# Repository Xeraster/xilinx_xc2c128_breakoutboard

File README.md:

a standalone breakout board for Xilinx xc2c128-7tqg144i cplds

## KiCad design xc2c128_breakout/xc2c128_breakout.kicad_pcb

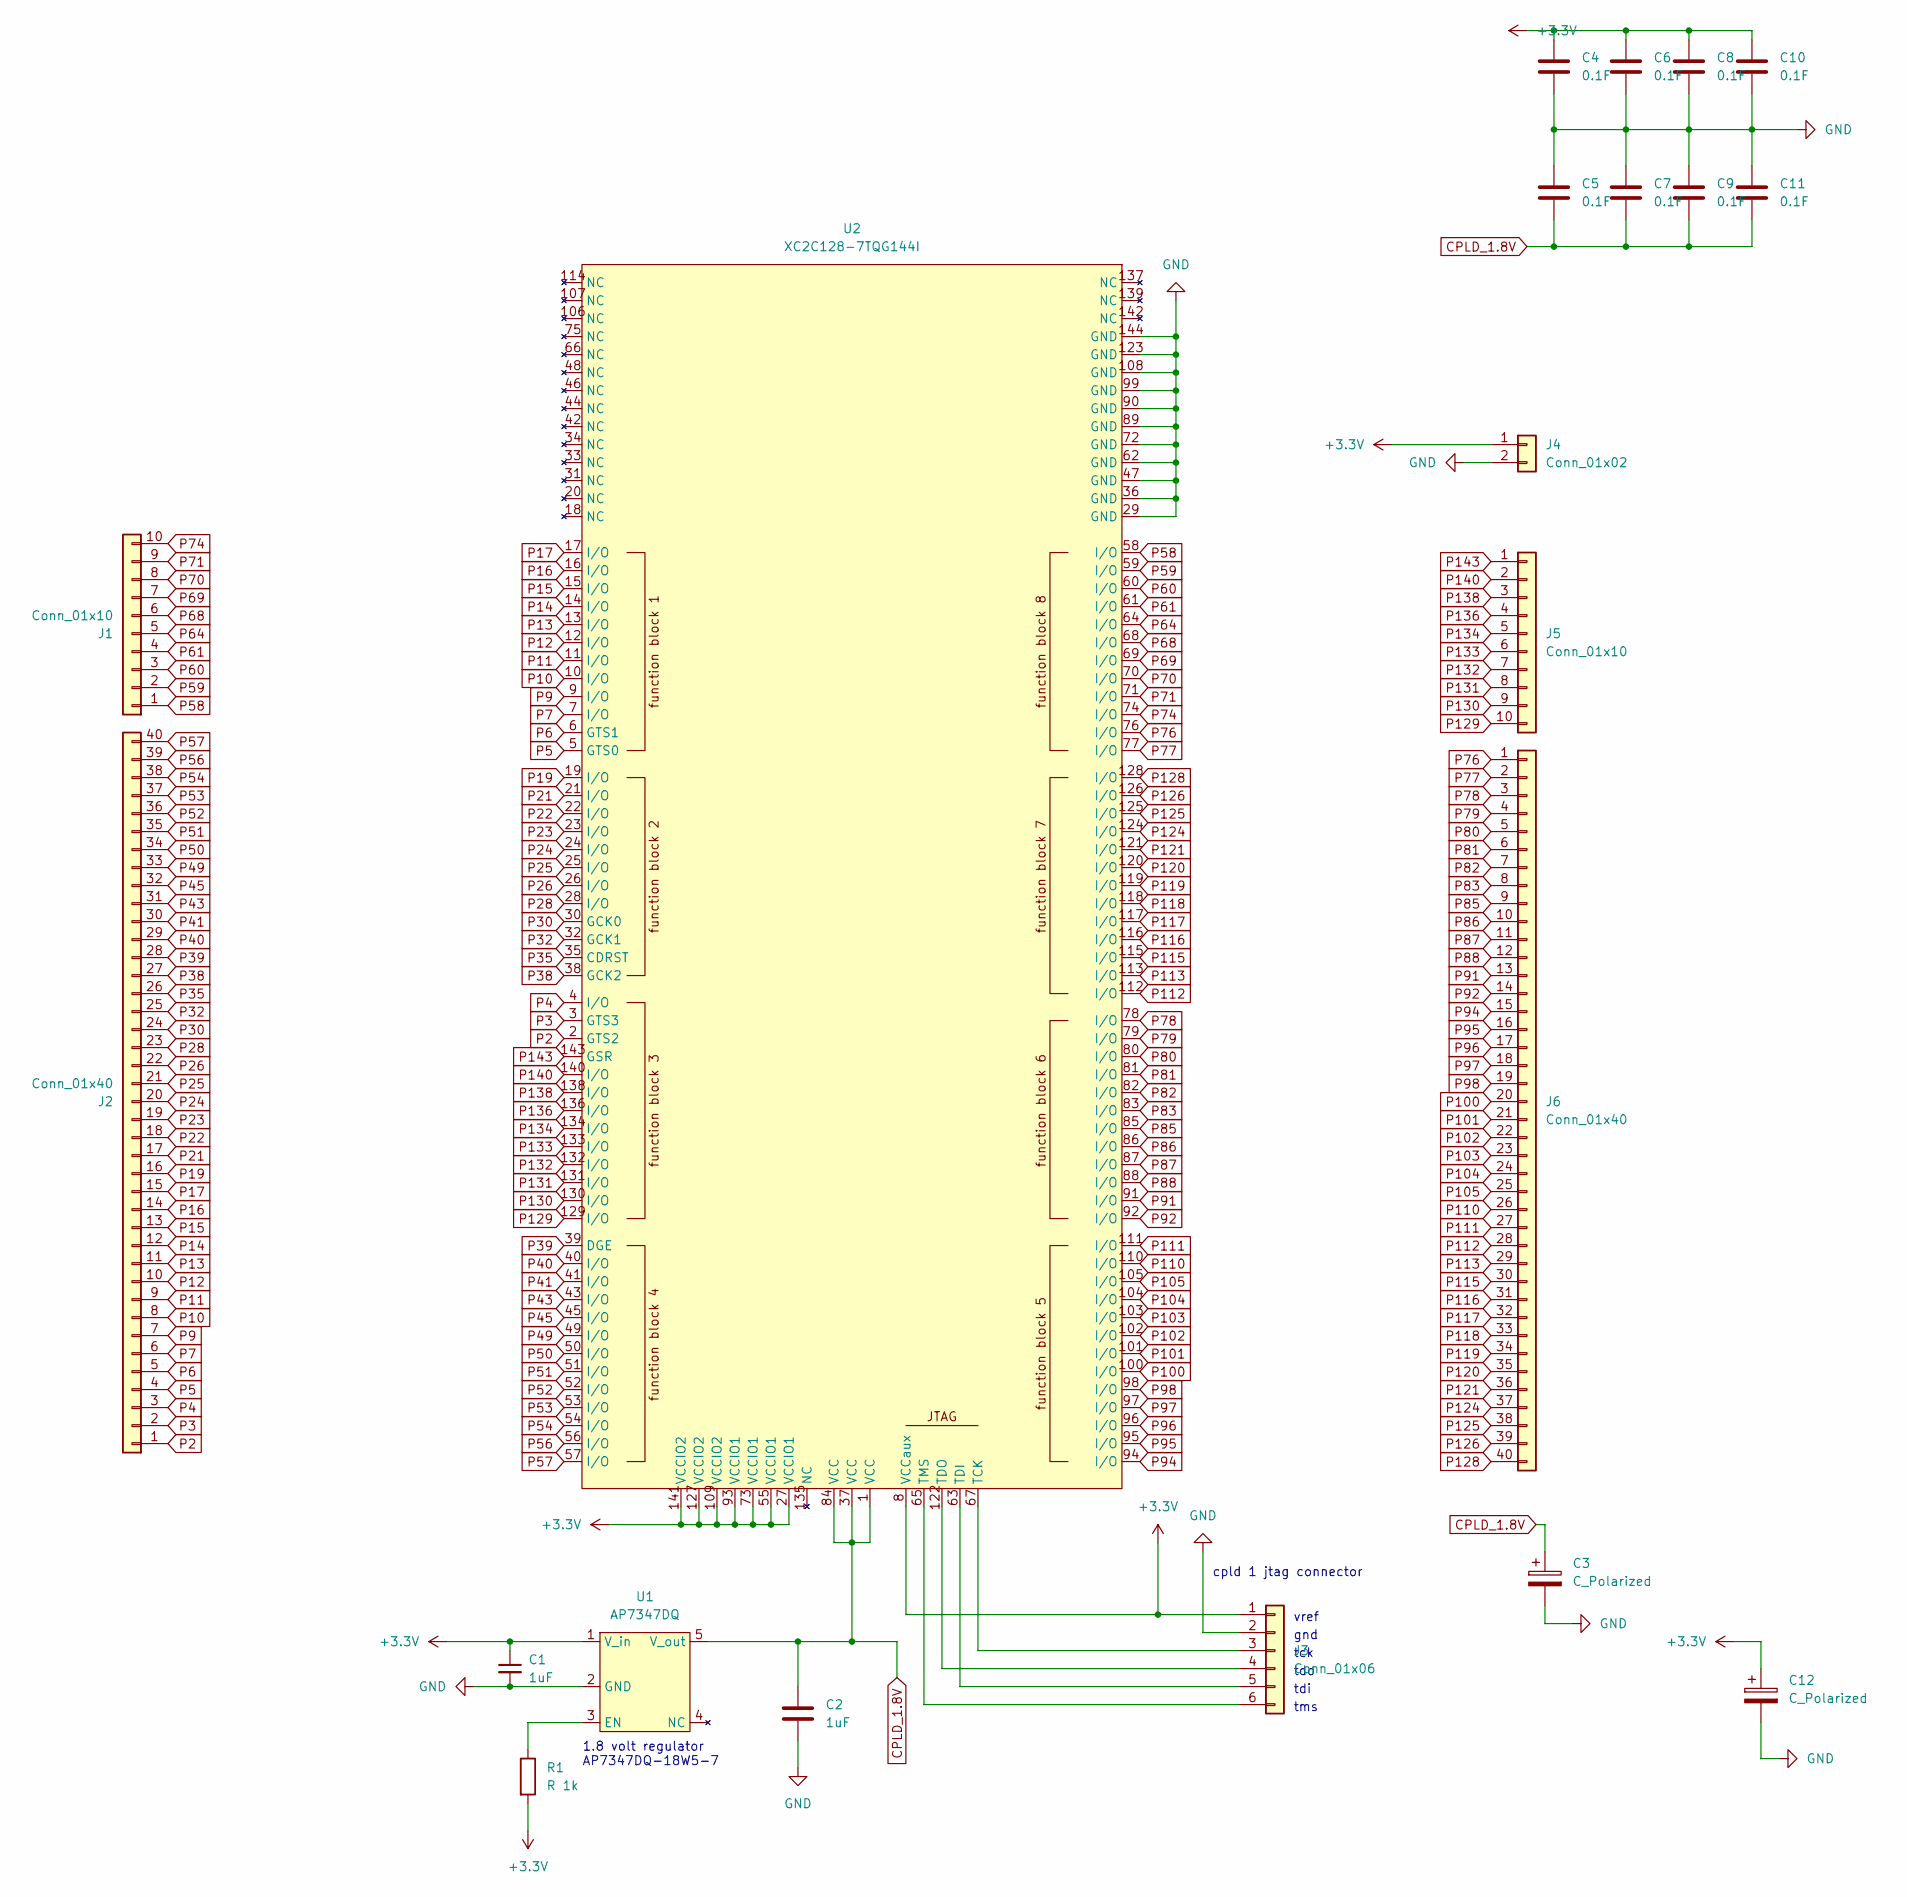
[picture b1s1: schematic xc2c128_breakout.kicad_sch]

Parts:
C1, C2: 1uF; C_Disc_D5.0mm_W2.5mm_P5.00mm
C3, C12: C_Polarized; CP_Radial_D5.0mm_P2.50mm
C4, C5, C6, C7, C8, C9, C10, C11: 0.1F; C_Disc_D5.0mm_W2.5mm_P5.00mm
J1, J5: Conn_01x10; PinHeader_1x10_P2.54mm_Vertical
J2, J6: Conn_01x40; PinHeader_1x40_P2.54mm_Vertical
J3: Conn_01x06; PinHeader_1x06_P2.54mm_Vertical
J4: Conn_01x02; PinHeader_1x02_P2.54mm_Vertical
R1: R 1k; R_Axial_DIN0207_L6.3mm_D2.5mm_P10.16mm_Horizontal
U1: AP7347DQ; SOT25
U2: XC2C128-7TQG144I; TQFP-144_20x20mm_P0.5mm

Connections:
+3.3V: C1.1, C4.1, C6.1, C8.1, C10.1, C12.1, J3.1, J4.1, R1.2, U1.1 (V_in), U2.8 (VCCaux), U2.27 (VCCIO1), U2.55 (VCCIO1), U2.73 (VCCIO1), U2.93 (VCCIO1), U2.109 (VCCIO2), U2.127 (VCCIO2), U2.141 (VCCIO2)
CPLD_1.8V: C2.1, C3.1, C5.2, C7.2, C9.2, C11.2, U1.5 (V_out), U2.1 (VCC), U2.37 (VCC), U2.84 (VCC)
GND: C1.2, C2.2, C3.2, C4.2, C5.1, C6.2, C7.1, C8.2, C9.1, C10.2, C11.1, C12.2, J3.2, J4.2, U1.2 (GND), U2.29 (GND), U2.36 (GND), U2.47 (GND), U2.62 (GND), U2.72 (GND), U2.89 (GND), U2.90 (GND), U2.99 (GND), U2.108 (GND), U2.123 (GND), U2.144 (GND)
unnamed: J3.3, U2.67 (TCK)
unnamed: J3.4, U2.122 (TDO)
unnamed: J3.5, U2.63 (TDI)
unnamed: J3.6, U2.65 (TMS)
unnamed: R1.1, U1.3 (EN)
P2: J2.1, U2.2 (GTS2)
P3: J2.2, U2.3 (GTS3)
P4: J2.3, U2.4 (I/O)
P5: J2.4, U2.5 (GTS0)
P6: J2.5, U2.6 (GTS1)
P7: J2.6, U2.7 (I/O)
P9: J2.7, U2.9 (I/O)
P10: J2.8, U2.10 (I/O)
P11: J2.9, U2.11 (I/O)
P12: J2.10, U2.12 (I/O)
P13: J2.11, U2.13 (I/O)
P14: J2.12, U2.14 (I/O)
P15: J2.13, U2.15 (I/O)
P16: J2.14, U2.16 (I/O)
P17: J2.15, U2.17 (I/O)
P19: J2.16, U2.19 (I/O)
P21: J2.17, U2.21 (I/O)
P22: J2.18, U2.22 (I/O)
P23: J2.19, U2.23 (I/O)
P24: J2.20, U2.24 (I/O)
P25: J2.21, U2.25 (I/O)
P26: J2.22, U2.26 (I/O)
P28: J2.23, U2.28 (I/O)
P30: J2.24, U2.30 (GCK0)
P32: J2.25, U2.32 (GCK1)
P35: J2.26, U2.35 (CDRST)
P38: J2.27, U2.38 (GCK2)
P39: J2.28, U2.39 (DGE)
P40: J2.29, U2.40 (I/O)
P41: J2.30, U2.41 (I/O)
P43: J2.31, U2.43 (I/O)
P45: J2.32, U2.45 (I/O)
P49: J2.33, U2.49 (I/O)
P50: J2.34, U2.50 (I/O)
P51: J2.35, U2.51 (I/O)
P52: J2.36, U2.52 (I/O)
P53: J2.37, U2.53 (I/O)
P54: J2.38, U2.54 (I/O)
P56: J2.39, U2.56 (I/O)
P57: J2.40, U2.57 (I/O)
P58: J1.1, U2.58 (I/O)
P59: J1.2, U2.59 (I/O)
P60: J1.3, U2.60 (I/O)
P61: J1.4, U2.61 (I/O)
P64: J1.5, U2.64 (I/O)
P68: J1.6, U2.68 (I/O)
P69: J1.7, U2.69 (I/O)
P70: J1.8, U2.70 (I/O)
P71: J1.9, U2.71 (I/O)
P74: J1.10, U2.74 (I/O)
P76: J6.1, U2.76 (I/O)
P77: J6.2, U2.77 (I/O)
P78: J6.3, U2.78 (I/O)
P79: J6.4, U2.79 (I/O)
P80: J6.5, U2.80 (I/O)
P81: J6.6, U2.81 (I/O)
P82: J6.7, U2.82 (I/O)
P83: J6.8, U2.83 (I/O)
P85: J6.9, U2.85 (I/O)
P86: J6.10, U2.86 (I/O)
P87: J6.11, U2.87 (I/O)
P88: J6.12, U2.88 (I/O)
P91: J6.13, U2.91 (I/O)
P92: J6.14, U2.92 (I/O)
P94: J6.15, U2.94 (I/O)
P95: J6.16, U2.95 (I/O)
P96: J6.17, U2.96 (I/O)
P97: J6.18, U2.97 (I/O)
P98: J6.19, U2.98 (I/O)
P100: J6.20, U2.100 (I/O)
P101: J6.21, U2.101 (I/O)
P102: J6.22, U2.102 (I/O)
P103: J6.23, U2.103 (I/O)
P104: J6.24, U2.104 (I/O)
P105: J6.25, U2.105 (I/O)
P110: J6.26, U2.110 (I/O)
P111: J6.27, U2.111 (I/O)
P112: J6.28, U2.112 (I/O)
P113: J6.29, U2.113 (I/O)
P115: J6.30, U2.115 (I/O)
P116: J6.31, U2.116 (I/O)
P117: J6.32, U2.117 (I/O)
P118: J6.33, U2.118 (I/O)
P119: J6.34, U2.119 (I/O)
P120: J6.35, U2.120 (I/O)
P121: J6.36, U2.121 (I/O)
P124: J6.37, U2.124 (I/O)
P125: J6.38, U2.125 (I/O)
P126: J6.39, U2.126 (I/O)
P128: J6.40, U2.128 (I/O)
P129: J5.10, U2.129 (I/O)
P130: J5.9, U2.130 (I/O)
P131: J5.8, U2.131 (I/O)
P132: J5.7, U2.132 (I/O)
P133: J5.6, U2.133 (I/O)
P134: J5.5, U2.134 (I/O)
P136: J5.4, U2.136 (I/O)
P138: J5.3, U2.138 (I/O)
P140: J5.2, U2.140 (I/O)
P143: J5.1, U2.143 (GSR)

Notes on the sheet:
tdo
vref
1.8 volt regulator AP7347DQ-18W5-7
tdi
tms
tck
cpld 1 jtag connector
gnd

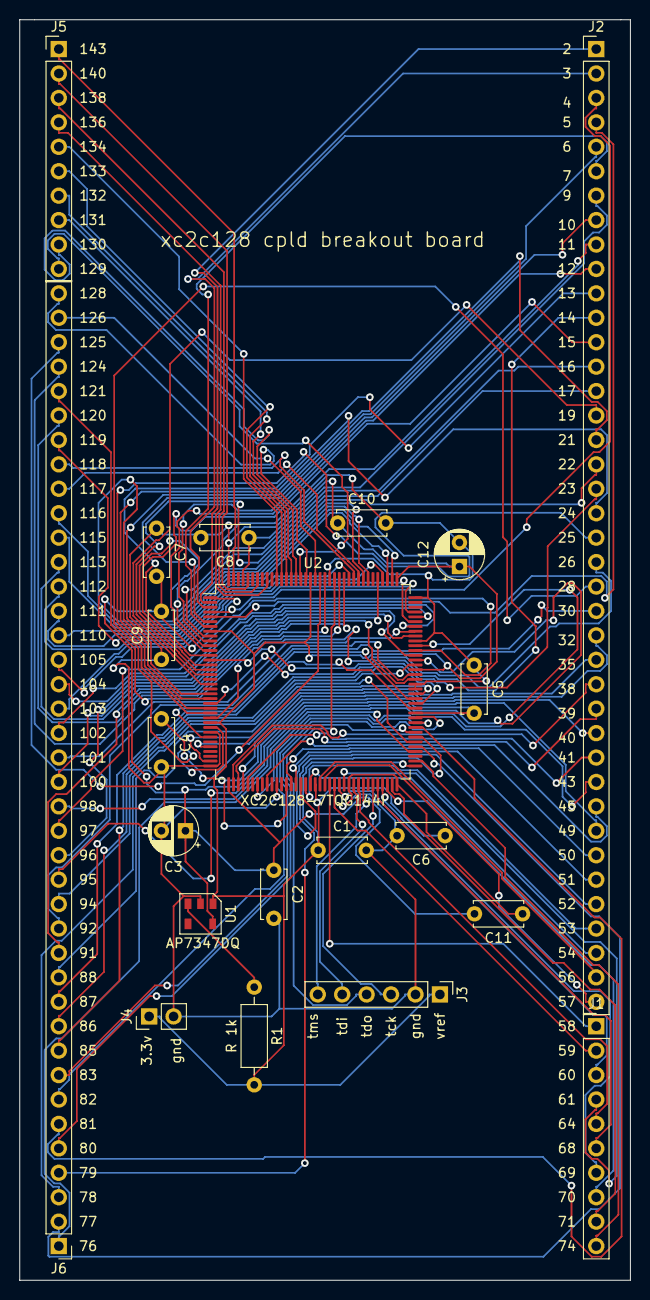
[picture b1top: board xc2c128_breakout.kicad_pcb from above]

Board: 2 copper layers, 63.5 x 131.1 mm, 21 parts (0 on the bottom side), 108 nets.
